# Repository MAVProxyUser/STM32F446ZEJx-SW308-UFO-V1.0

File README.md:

STM32F446ZEJx UFBGA144 Target Board for ChipWhisperer

* [STM32F446ZEJx-SW308-UFO-V1.0](#stm32f446zejx-sw308-ufo-v10)
   * [Jumpers](#jumpers)
   * [Schematic](#schematic)
   * [Testing Blanks &amp; Real Paprium](#testing-blanks--real-paprium)

It is no secret that I am affiliated with the group of people focusing on [efforts to dump the Watermelon Games Paprium cart](https://github.com/ArcadeHustle/WatermelonPapriumDump). As part of this effort there became a need to 
attack an STM32F4 based chip. Sadly that chip wound up being in RDP2 mode, but the resulting tool that was created serves a greater purpose, so it is being shared here. 

At the time the work effort was put forth there was no UFBGA144 compatible Target Board for ChipWhisperer, so we worked with a trusted PCB design partner [@javier-rodas](https://github.com/javier-rodas) owner of SEVENIX INGENIERIA & the [@XTREME-MISTER](https://github.com/XTREME-MISTER) project to work out what was needed. This board will connect easily to a STLink V2, 
or a ChipWhisperer depending on where the jumpers are placed. The initial project this board was created for never moved past the STLink jumpers, we immediatly found that the chip was fully protected with all debug interfaced 
disabled. 

None the less, this is a perfect platform for learning Chip Whisperer based glitching logic, or attacking other UFBGA144 STM32 chips. 

# STM32F446ZEJx-SW308-UFO-V1.0

[Documentation](https://github.com/MAVProxyUser/STM32F446ZEJx-SW308-UFO-V1.0/tree/main/STM32F446ZEJx-SW308-UFO%20V1.0/DOCS) is fairly simple, set the jumpers accordingly, treat it as you would any other ChipWhisperer target board. 

## Jumpers
Enable jumpers as follows for CW usage. 

## Schematic
You can see how the jumpers impact the schematic below.  

## Testing Blanks & Real Paprium 
We tested this design with a number of now rare blank STM32F446ZEJ6 chips, as well as an excavated STM32 from a Paprium game cart. 

If you need an amazing PCB designer, please let me know, and I can put you in touch with one.

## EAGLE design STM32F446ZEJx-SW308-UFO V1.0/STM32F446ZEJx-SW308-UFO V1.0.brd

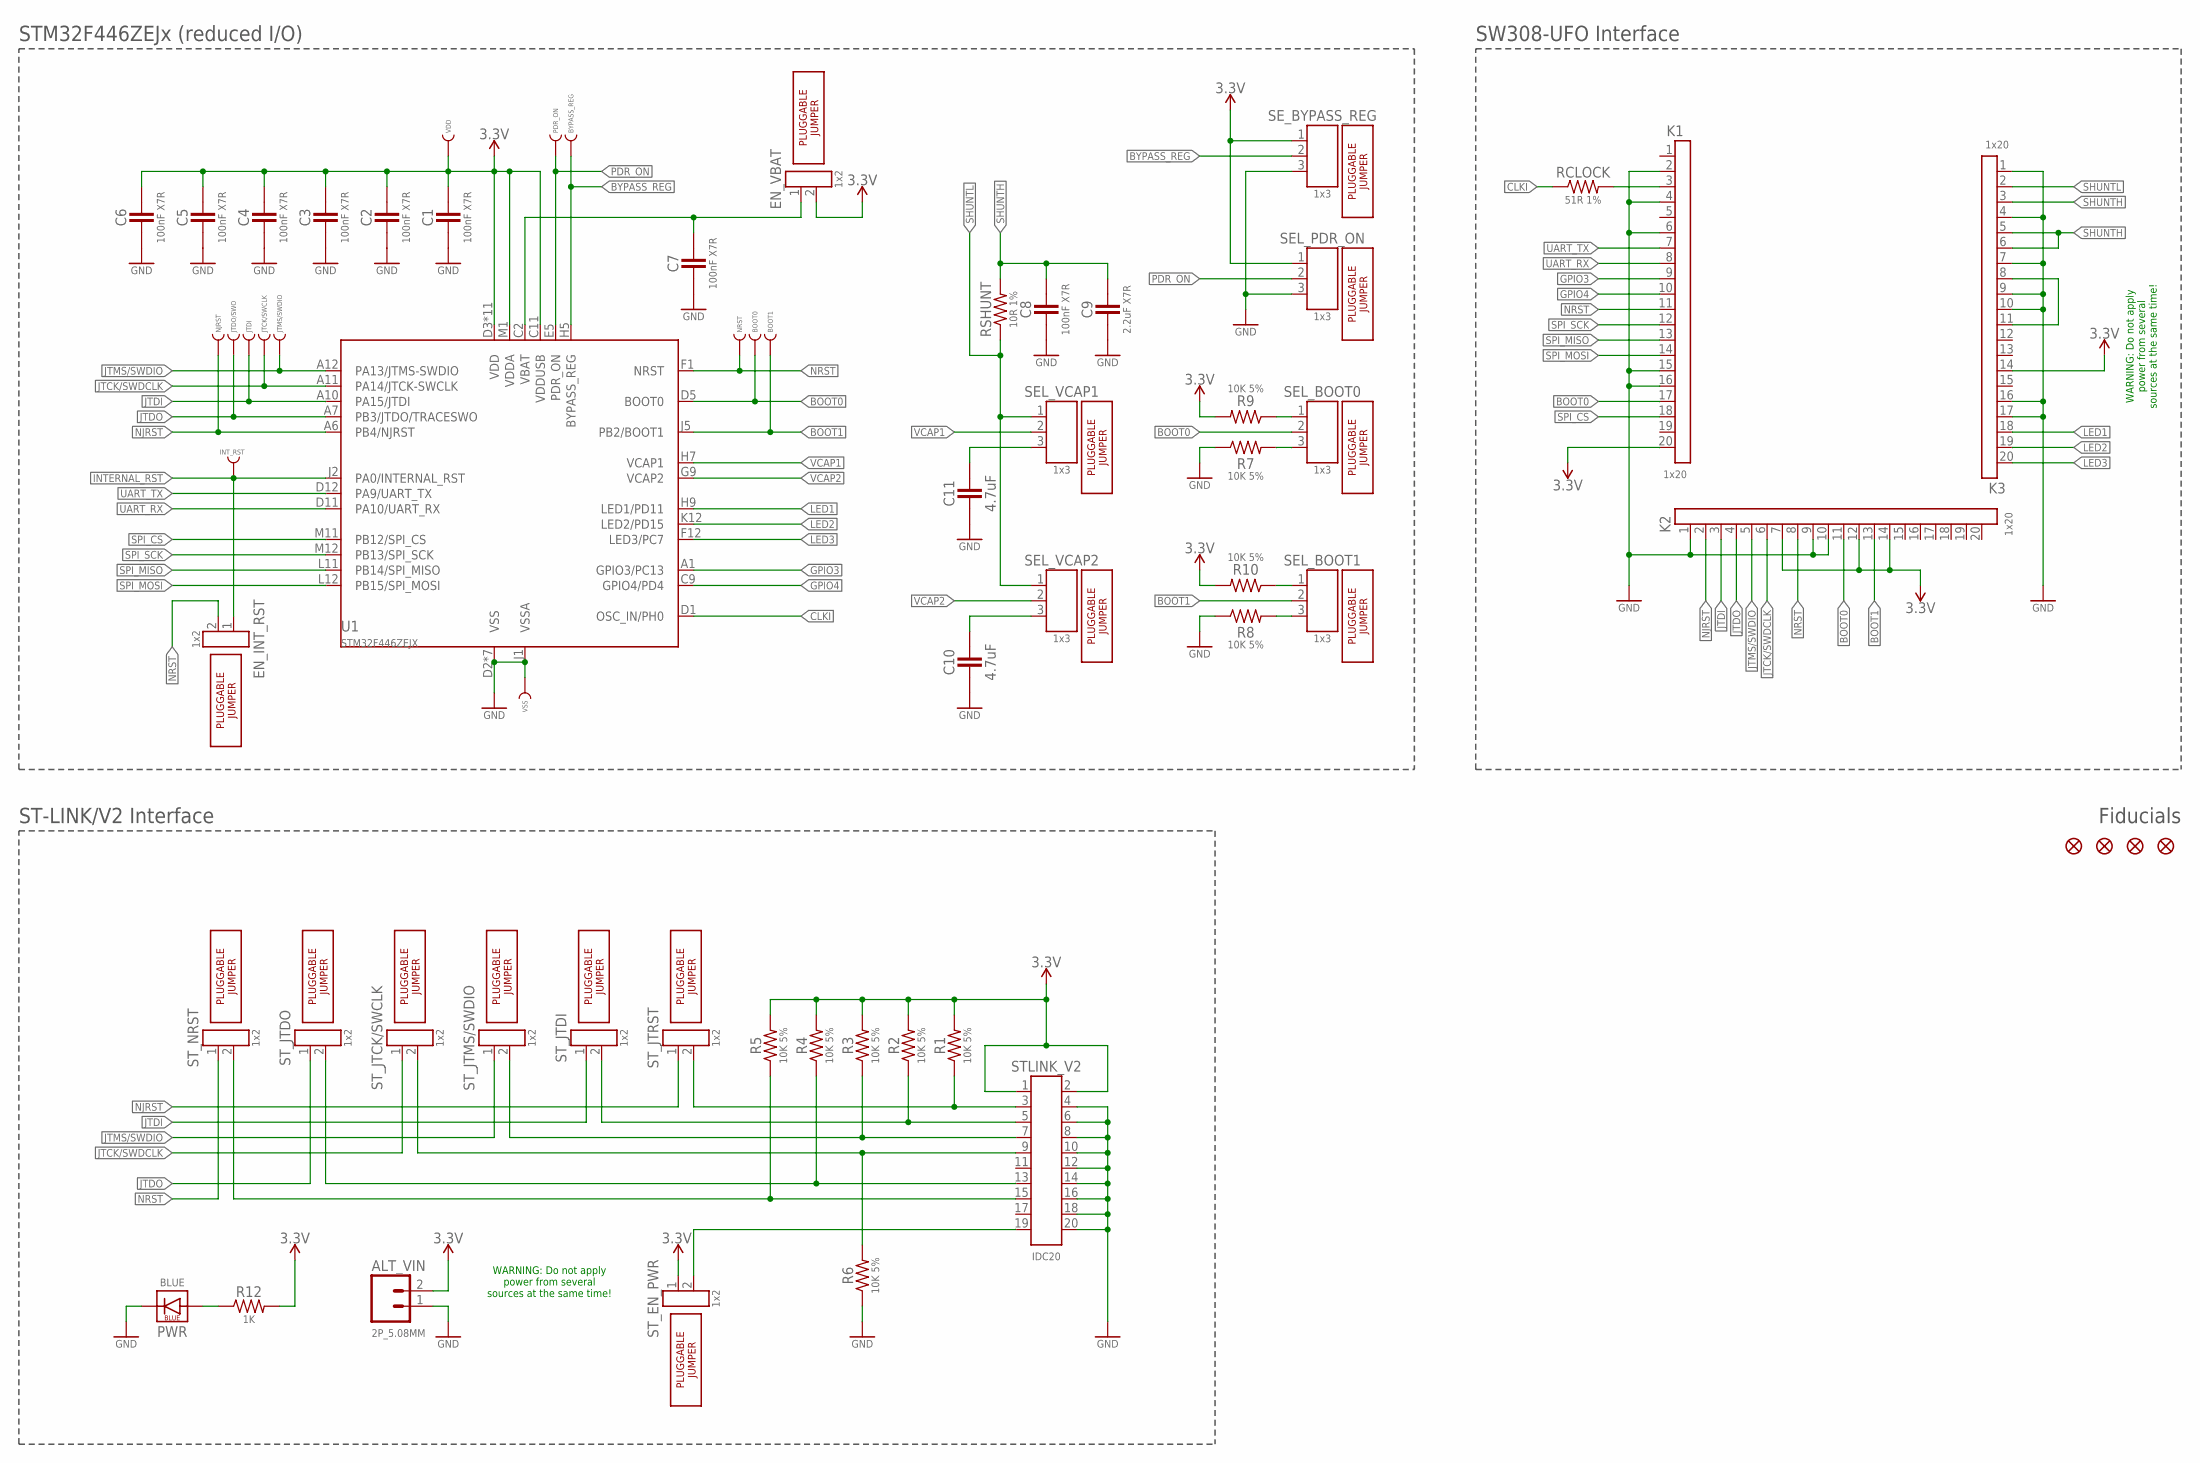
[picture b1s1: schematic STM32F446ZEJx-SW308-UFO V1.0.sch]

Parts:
ALT_VIN: 2P_5.08MM; BORNA_2X5.08MM_NINGBO-KANGNEX-ELEC_WJ500V-5.08-2P
BOOT0, BOOT1: TESTPOINT_TH_0.8MM; 1X01
BYPASS_REG: TESTPOINT_TH_0.8MM; 1X01
C1, C2, C3, C4, C5, C6, C7, C8: 100nF X7R; 0603_IPC_NOMINAL; LCSC_PN C1591
C9: 2.2uF X7R; 0603_IPC_NOMINAL; LCSC_PN C100082
C10, C11: 4.7uF; 0603_IPC_NOMINAL; LCSC_PN C8032
EN_INT_RST: 1x2; M1X2_GREENCONN_GPHA101-0201A001A1BA(A=6,B=3)_ALT_PADS
EN_VBAT: 1x2; M1X2_GREENCONN_GPHA101-0201A001A1BA(A=6,B=3)_ALT_PADS
FD1, FD5, FD7, FD9: FIDUCIAL_MICRO; FIDUCIAL-MICRO
INT_RST: TESTPOINT_TH_0.8MM; 1X01
JTCK/SWCLK: TESTPOINT_TH_0.8MM; 1X01
JTDI: TESTPOINT_TH_0.8MM; 1X01
JTDO/SWO: TESTPOINT_TH_0.8MM; 1X01
JTMS/SWDIO: TESTPOINT_TH_0.8MM; 1X01
JUMPER1, JUMPER2, JUMPER3, JUMPER4, JUMPER5, JUMPER6, JUMPER7, JUMPER8, JUMPER9, JUMPER10, JUMPER11, JUMPER12, JUMPER13, JUMPER14, JUMPER15: JUMPER_2.54MM
K1, K2, K3: 1x20; M1X20_2.54MM_LOCK_BOOMELE_C50981
NJRST: TESTPOINT_TH_0.8MM; 1X01
NRST: TESTPOINT_TH_0.8MM; 1X01
PDR_ON: TESTPOINT_TH_0.8MM; 1X01
PWR: BLUE; 0603-BLUE-LED
R1, R2, R3, R4, R5, R6, R7, R8, R9, R10: 10K 5%; 0603_IPC_NOMINAL; LCSC_PN C99198
R12: 1K; 0603_IPC_NOMINAL; LCSC_PN C22548
RCLOCK: 51R 1%; 0603_IPC_NOMINAL; LCSC_PN C114628
RSHUNT: 10R 1%; 0603_IPC_NOMINAL; LCSC_PN C109318
SEL_BOOT0, SEL_BOOT1: 1x3; M1X3_GREENCONN_GPHA101-0301A001A1BA(A=6,B=3)_ALT_PADS
SEL_PDR_ON: 1x3; M1X3_GREENCONN_GPHA101-0301A001A1BA(A=6,B=3)_ALT_PADS
SEL_VCAP1, SEL_VCAP2: 1x3; M1X3_GREENCONN_GPHA101-0301A001A1BA(A=6,B=3)_ALT_PADS
SE_BYPASS_REG: 1x3; M1X3_GREENCONN_GPHA101-0301A001A1BA(A=6,B=3)_ALT_PADS
STLINK_V2: IDC20; M2X10_2.54MM_IDC_SHROUDED__JLIN_321020SG0ABK00A01_C429961
ST_EN_PWR: 1x2; M1X2_GREENCONN_GPHA101-0201A001A1BA(A=6,B=3)_ALT_PADS
ST_JTCK/SWCLK: 1x2; M1X2_GREENCONN_GPHA101-0201A001A1BA(A=6,B=3)_ALT_PADS
ST_JTDI: 1x2; M1X2_GREENCONN_GPHA101-0201A001A1BA(A=6,B=3)_ALT_PADS
ST_JTDO: 1x2; M1X2_GREENCONN_GPHA101-0201A001A1BA(A=6,B=3)_ALT_PADS
ST_JTMS/SWDIO: 1x2; M1X2_GREENCONN_GPHA101-0201A001A1BA(A=6,B=3)_ALT_PADS
ST_JTRST: 1x2; M1X2_GREENCONN_GPHA101-0201A001A1BA(A=6,B=3)_ALT_PADS
ST_NRST: 1x2; M1X2_GREENCONN_GPHA101-0201A001A1BA(A=6,B=3)_ALT_PADS
U1: STM32F446ZEJX
VDD: TESTPOINT_TH_0.8MM; 1X01
VSS: TESTPOINT_TH_0.8MM; 1X01

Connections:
3.3V: ALT_VIN.2, C1.1, C2.1, C3.1, C4.1, C5.1, C6.1, EN_VBAT.2, K1.20, K2.7, K2.12, K2.14, K3.14, R1.2, R2.2, R3.2, R4.2, R5.2, R9.2, R10.2, R12.2, SEL_PDR_ON.1, SE_BYPASS_REG.1, STLINK_V2.1, STLINK_V2.2, ST_EN_PWR.1, U1.C11 (VDDUSB), U1.D3 (VDD), U1.F4 (VDD), U1.F5 (VDD), U1.F6 (VDD), U1.F7 (VDD), U1.F8 (VDD), U1.F9 (VDD), U1.F10 (VDD), U1.G5 (VDD), U1.G6 (VDD), U1.G7 (VDD), U1.M1 (VDDA), VDD.1
BOOT0: BOOT0.1, K1.17, K2.11, SEL_BOOT0.2, U1.D5 (BOOT0)
BOOT1: BOOT1.1, K2.13, SEL_BOOT1.2, U1.J5 (PB2/BOOT1)
BYPASS_REG: BYPASS_REG.1, SE_BYPASS_REG.2, U1.H5 (BYPASS_REG)
CLKI: RCLOCK.1, U1.D1 (OSC_IN/PH0)
GND: ALT_VIN.1, C1.2, C2.2, C3.2, C4.2, C5.2, C6.2, C7.2, C8.2, C9.2, C10.2, C11.2, K1.2, K1.4, K1.6, K1.15, K1.16, K2.1, K2.9, K2.10, K3.1, K3.4, K3.7, K3.9, K3.10, K3.16, K3.17, PWR.CATHODE (C), R6.1, R7.1, R8.1, SEL_PDR_ON.3, SE_BYPASS_REG.3, STLINK_V2.4, STLINK_V2.6, STLINK_V2.8, STLINK_V2.10, STLINK_V2.12, STLINK_V2.14, STLINK_V2.16, STLINK_V2.18, STLINK_V2.20, U1.D2 (VSS), U1.E6 (VSS), U1.E7 (VSS), U1.G4 (VSS), U1.G8 (VSS), U1.G10 (VSS), U1.H6 (VSS), U1.J1 (VSSA), VSS.1
GPIO3: K1.9, U1.A1 (GPIO3/PC13)
GPIO4: K1.10, U1.C9 (GPIO4/PD4)
INTERNAL_RST: EN_INT_RST.1, INT_RST.1, U1.J2 (PA0/INTERNAL_RST)
JTCK/SWDCLK: JTCK/SWCLK.1, K2.6, ST_JTCK/SWCLK.1, U1.A11 (PA14/JTCK-SWCLK)
JTDI: JTDI.1, K2.3, ST_JTDI.1, U1.A10 (PA15/JTDI)
JTDO: JTDO/SWO.1, K2.4, ST_JTDO.1, U1.A7 (PB3/JTDO/TRACESWO)
JTMS/SWDIO: JTMS/SWDIO.1, K2.5, ST_JTMS/SWDIO.1, U1.A12 (PA13/JTMS-SWDIO)
LED1: K3.18, U1.H9 (LED1/PD11)
LED2: K3.19, U1.K12 (LED2/PD15)
LED3: K3.20, U1.F12 (LED3/PC7)
unnamed: R2.1, STLINK_V2.5, ST_JTDI.2
unnamed: C7.1, EN_VBAT.1, U1.C2 (VBAT)
unnamed: PWR.ANODE (A), R12.1
unnamed: R3.1, STLINK_V2.7, ST_JTMS/SWDIO.2
unnamed: C10.1, SEL_VCAP2.3
unnamed: R1.1, STLINK_V2.3, ST_JTRST.2
unnamed: R6.2, STLINK_V2.9, ST_JTCK/SWCLK.2
unnamed: R7.2, SEL_BOOT0.3
unnamed: R4.1, STLINK_V2.13, ST_JTDO.2
unnamed: R10.1, SEL_BOOT1.1
unnamed: R5.1, STLINK_V2.15, ST_NRST.2
unnamed: R8.2, SEL_BOOT1.3
unnamed: STLINK_V2.19, ST_EN_PWR.2
unnamed: C11.1, SEL_VCAP1.3
unnamed: R9.1, SEL_BOOT0.1
unnamed: K3.8, K3.11
unnamed: K1.3, RCLOCK.2
NJRST: K2.2, NJRST.1, ST_JTRST.1, U1.A6 (PB4/NJRST)
NRST: EN_INT_RST.2, K1.11, K2.8, NRST.1, ST_NRST.1, U1.F1 (NRST)
PDR_ON: PDR_ON.1, SEL_PDR_ON.2, U1.E5 (PDR_ON)
SHUNTH: C8.1, C9.1, K3.3, K3.5, K3.6, RSHUNT.2
SHUNTL: K3.2, RSHUNT.1, SEL_VCAP1.1, SEL_VCAP2.1
SPI_CS: K1.18, U1.M11 (PB12/SPI_CS)
SPI_MISO: K1.13, U1.L11 (PB14/SPI_MISO)
SPI_MOSI: K1.14, U1.L12 (PB15/SPI_MOSI)
SPI_SCK: K1.12, U1.M12 (PB13/SPI_SCK)
UART_RX: K1.8, U1.D11 (PA10/UART_RX)
UART_TX: K1.7, U1.D12 (PA9/UART_TX)
VCAP1: SEL_VCAP1.2, U1.H7 (VCAP1)
VCAP2: SEL_VCAP2.2, U1.G9 (VCAP2)

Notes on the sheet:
STM32F446ZEJx (reduced I/O)
ST-LINK/V2 Interface
WARNING: Do not apply power from several sources at the same time!
SW308-UFO Interface
Fiducials

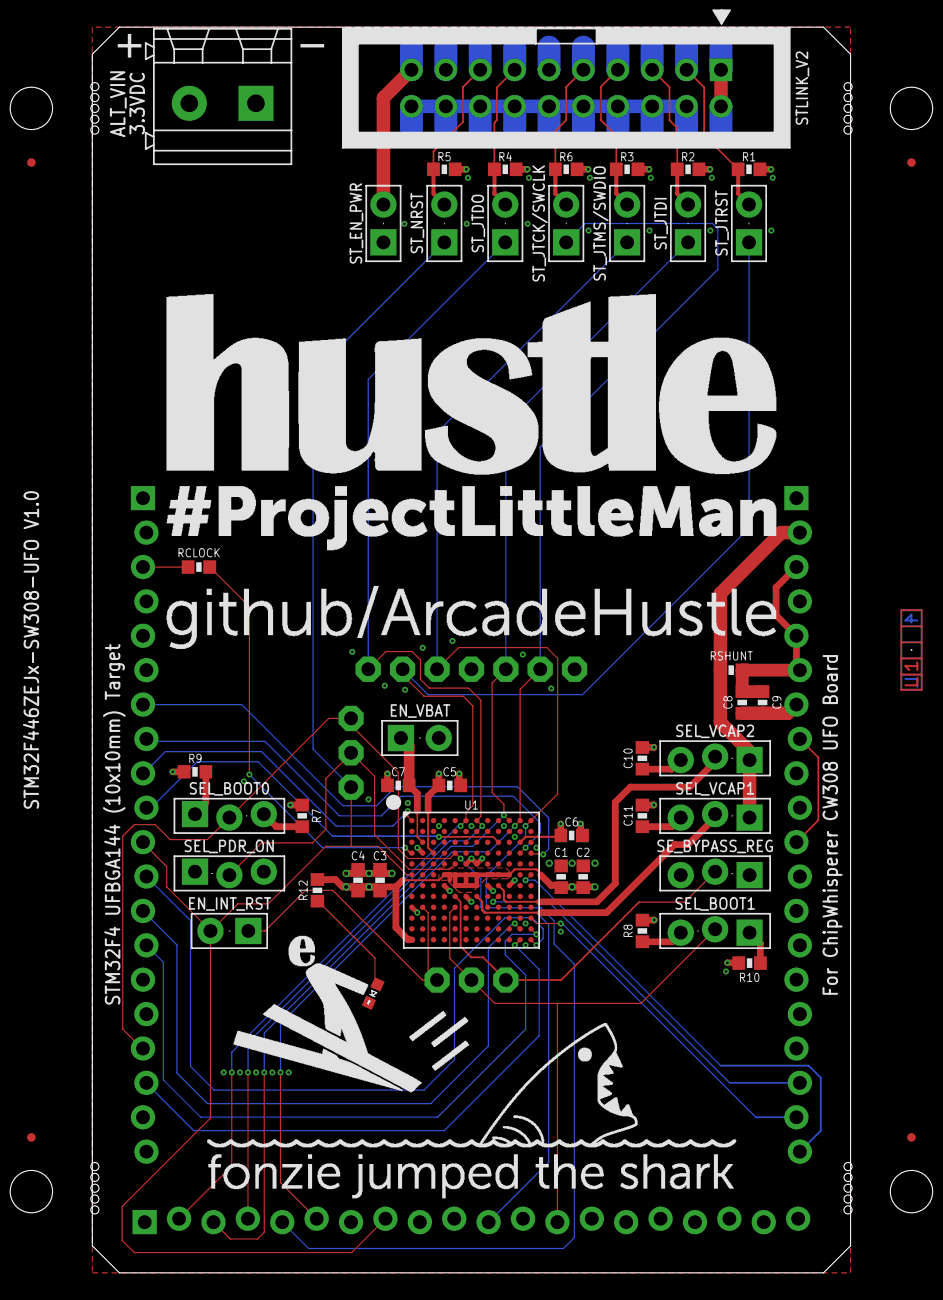
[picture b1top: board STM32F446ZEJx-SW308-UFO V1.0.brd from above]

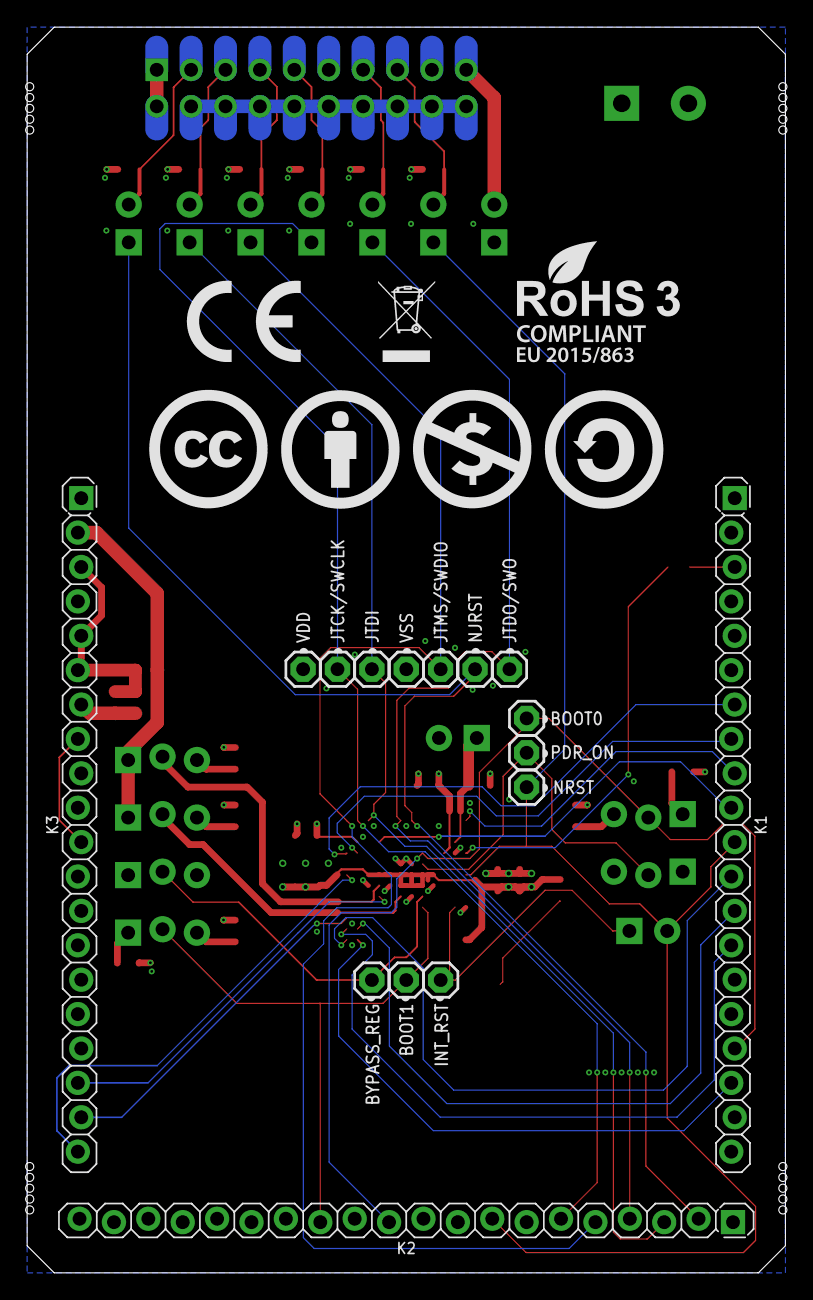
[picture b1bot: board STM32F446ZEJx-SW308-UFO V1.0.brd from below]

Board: 4 copper layers, 56.0 x 92.0 mm, 85 parts (20 on the bottom side), 46 nets.

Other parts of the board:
U$1: 1234_MULTI-LAYER_PCB-INSPECTION
U$2: GITHUB_ARCADEHUSLE_PROJECTLITTLEMAN_2_BOTTOM_45MM
U$3: GITHUB_ARCADEHUSLE_PROJECTLITTLEMAN_2_TOP_45MM
U$4: CE_ICON_6MM
U$5: WEEE_ICON_6MM
U$6: ROHS3_COMPLIANT_ICON_6MM-8.98MM
U$8: ICON_CC-BY-NC-SA-4.0_H=8.7MM

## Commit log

2023-01-08 cosmetic + self dox

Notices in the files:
parts and their libraries:
SparkFun-PowerSymbols: Licensing: Creative Commons ShareAlike 4.0 International - https://creativecommons.org/licenses/by-sa/4.0
ArcadeHustle: (C) 2022 ArcadeHustle
